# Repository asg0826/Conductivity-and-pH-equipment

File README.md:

# Conductivity-and-pH-equipment

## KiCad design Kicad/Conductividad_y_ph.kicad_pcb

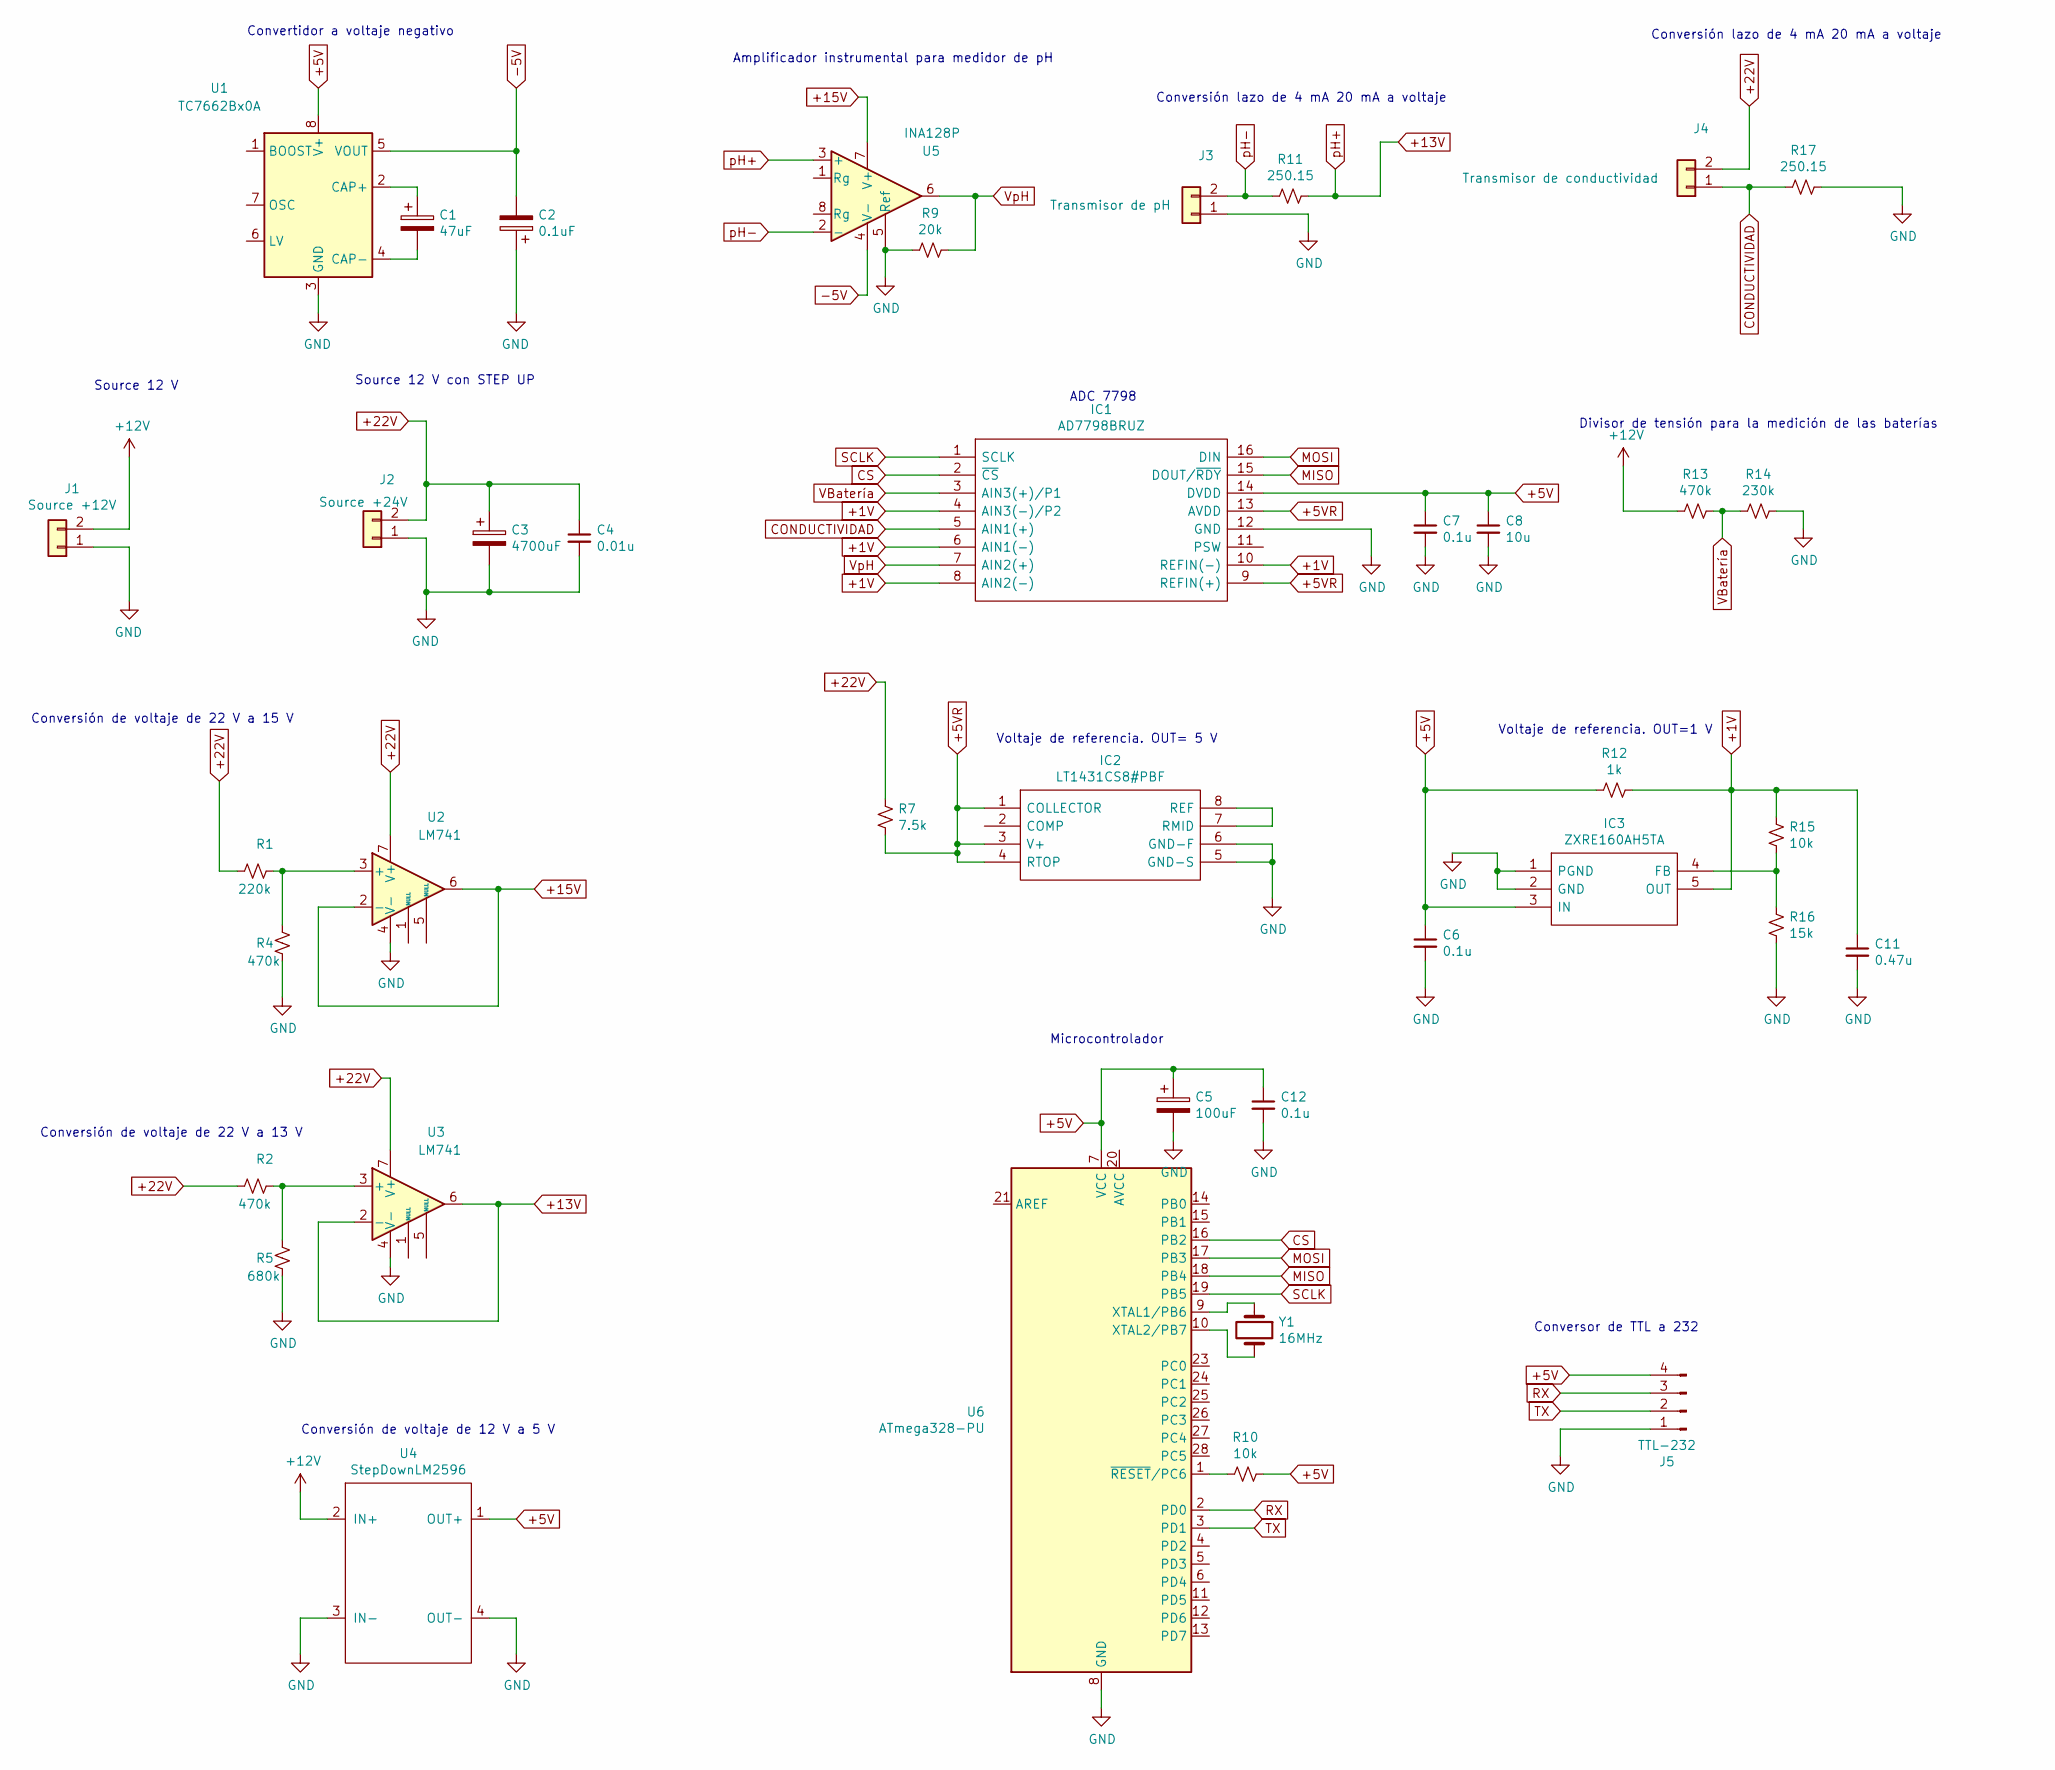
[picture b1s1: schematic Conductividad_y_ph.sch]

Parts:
C1: 47uF; CP_Radial_D5.0mm_P2.50mm
C2: 0.1uF; CP_Radial_D5.0mm_P2.50mm
C3: 4700uF; 4700uF_footPrint
C4: 0.01u; Tantalum_5.08mm
C5: 100uF; CP_Radial_D5.0mm_P2.50mm
C6, C7, C12: 0.1u; Tantalum_5.08mm
C8: 10u; Tantalum_5.08mm
C11: 0.47u; Tantalum_5.08mm
IC1: AD7798BRUZ; AD7798; Manufacturer_Part_Number AD7798BRUZ; Mouser Part Number 584-AD7798BRUZ
IC2: LT1431CS8#PBF; DIP-8_W7.62mm_Socket; Manufacturer_Part_Number LT1431CS8#PBF; Mouser Part Number 584-LT1431CS8#PBF
IC3: ZXRE160AH5TA; Regulator1V3; Manufacturer_Part_Number ZXRE160AH5TA; Mouser Part Number 522-ZXRE160AH5TA
J1: Source +12V; Conector2
J2: Source +24V; Conector2
J3: Transmisor de pH; Conector2
J4: Transmisor de conductividad; Conector2
J5: TTL-232; FanPinHeader_1x04_P2.54mm_Vertical
R1: 220k; R_Axial_DIN0207_L6.3mm_D2.5mm_P7.62mm_Horizontal
R2, R4, R13: 470k; R_Axial_DIN0207_L6.3mm_D2.5mm_P7.62mm_Horizontal
R5: 680k; R_Axial_DIN0207_L6.3mm_D2.5mm_P7.62mm_Horizontal
R7: 7.5k; R_Axial_DIN0207_L6.3mm_D2.5mm_P7.62mm_Horizontal
R9: 20k; R_Axial_DIN0207_L6.3mm_D2.5mm_P7.62mm_Horizontal
R10, R15: 10k; R_Axial_DIN0207_L6.3mm_D2.5mm_P7.62mm_Horizontal
R11, R17: 250.15; R_Axial_DIN0207_L6.3mm_D2.5mm_P15.24mm_Horizontal
R12: 1k; R_Axial_DIN0207_L6.3mm_D2.5mm_P7.62mm_Horizontal
R14: 230k; R_Axial_DIN0207_L6.3mm_D2.5mm_P7.62mm_Horizontal
R16: 15k; R_Axial_DIN0207_L6.3mm_D2.5mm_P7.62mm_Horizontal
U1: TC7662Bx0A; DIP-8_W7.62mm_Socket
U2, U3: LM741; DIP-8_W7.62mm_Socket
U4: StepDownLM2596; StepDownLm2596
U5: INA128P; DIP-8_W7.62mm_Socket
U6: ATmega328-PU; DIP-28_W7.62mm
Y1: 16MHz; Oscillator_16Mhz

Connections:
+1V: C11.1, IC1.4 (AIN3(-)/P2), IC1.6 (AIN1(-)), IC1.8 (AIN2(-)), IC1.10 (REFIN(-)), IC3.5 (OUT), R12.1, R15.1
+5V: C5.1, C6.1, C7.1, C8.1, C12.1, IC1.14 (DVDD), IC3.3 (IN), J5.4, R10.1, R12.2, U1.8 (V+), U4.1 (OUT+), U6.7 (VCC)
+5VR: IC1.9 (REFIN(+)), IC1.13 (AVDD), IC2.1 (COLLECTOR), IC2.3 (V+), IC2.4 (RTOP), R7.2
+12V: J1.2, R13.2, U4.2 (IN+); also elsewhere on the board
+13V: R11.1, U3.2 (-), U3.6, U5.3 (+)
+15V: U2.2 (-), U2.6, U5.7 (V+)
+22V: C3.1, C4.1, J2.2, J4.2, R1.2, R2.2, R7.1, U2.7 (V+), U3.7 (V+)
-5V: C2.2, U1.5 (VOUT), U5.4 (V-)
CONDUCTIVIDAD: IC1.5 (AIN1(+)), J4.1, R17.2
CS: IC1.2 (~CS), U6.16 (PB2)
GND: C2.1, C3.2, C4.2, C5.2, C6.2, C7.2, C8.2, C11.2, C12.2, IC1.12 (GND), IC2.5 (GND-S), IC2.6 (GND-F), IC3.1 (PGND), IC3.2 (GND), J1.1, J2.1, J3.1, J5.1, R4.2, R5.2, R9.2, R14.1, R16.2, R17.1, U1.3 (GND), U2.4 (V-), U3.4 (V-), U4.3 (IN-), U4.4 (OUT-), U5.5 (Ref), U6.8 (GND), U6.22 (GND); also elsewhere on the board
MISO: IC1.15 (DOUT/~RDY), U6.18 (PB4)
MOSI: IC1.16 (DIN), U6.17 (PB3)
unnamed: C1.1, U1.2 (CAP+)
unnamed: C1.2, U1.4 (CAP-)
unnamed: IC2.7 (RMID), IC2.8 (REF)
unnamed: IC3.4 (FB), R15.2, R16.1
unnamed: R1.1, R4.1, U2.3 (+)
unnamed: R2.1, R5.1, U3.3 (+)
unnamed: R10.2, U6.1 (~RESET~/PC6)
unnamed: U6.9 (XTAL1/PB6), Y1.1
unnamed: U6.10 (XTAL2/PB7), Y1.2
RX: J5.3, U6.2 (PD0)
SCLK: IC1.1 (SCLK), U6.19 (PB5)
TX: J5.2, U6.3 (PD1)
VBatería: IC1.3 (AIN3(+)/P1), R13.1, R14.2
VpH: IC1.7 (AIN2(+)), R9.1, U5.6
pH-: J3.2, R11.2, U5.2 (-)

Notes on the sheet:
Divisor de tensión para la medición de las baterías
Voltaje de referencia. OUT= 5 V
Voltaje de referencia. OUT=1 V
ADC 7798
Source 12 V
Amplificador instrumental para medidor de pH
Conversión lazo de 4 mA 20 mA a voltaje
Conversor de TTL a 232
Conversión de voltaje de 12 V a 5 V
Conversión de voltaje de 22 V a 13 V
Conversión de voltaje de 22 V a 15 V
Source 12 V con STEP UP
Microcontrolador
Convertidor a voltaje negativo

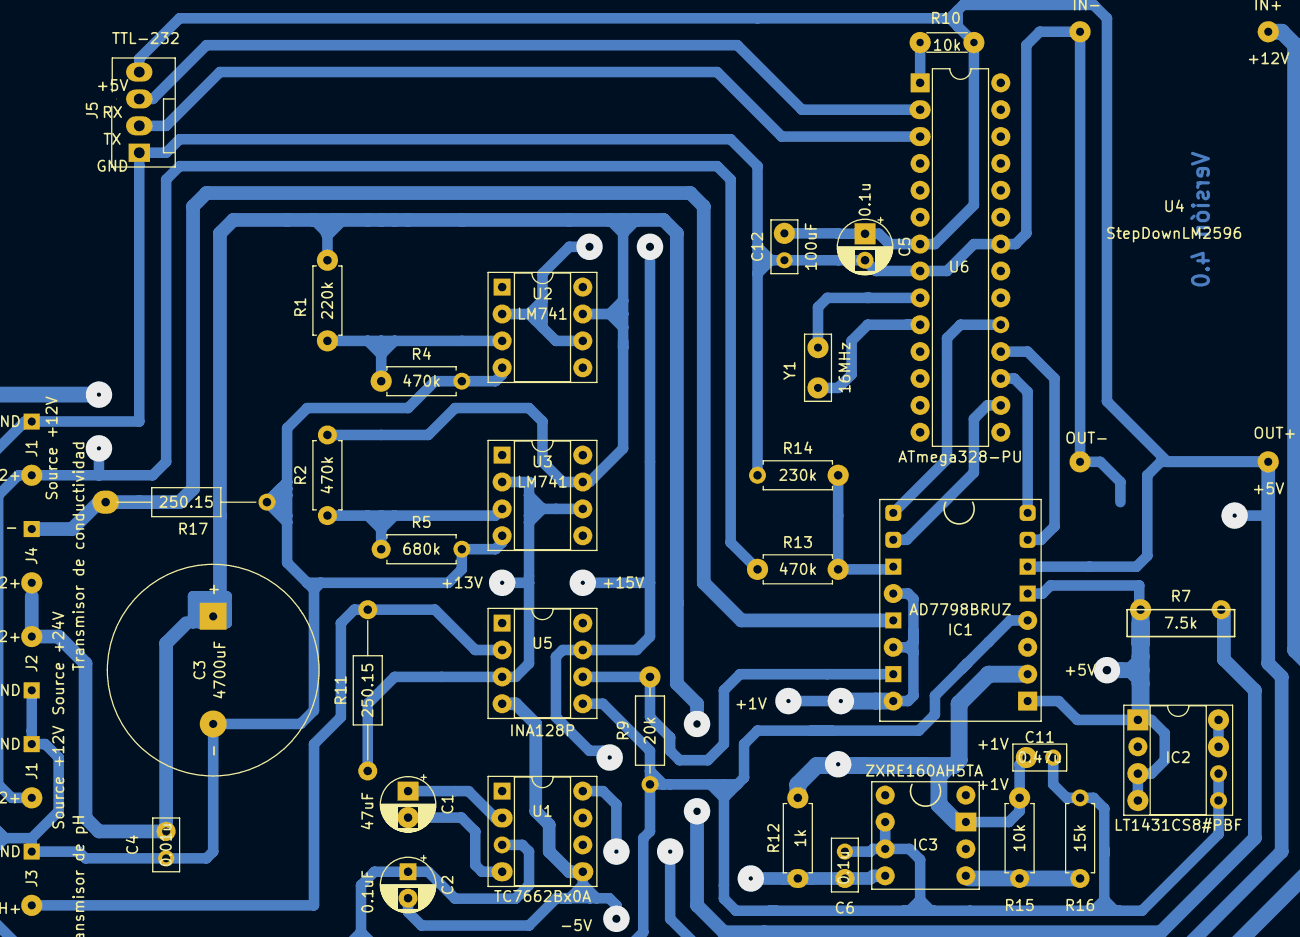
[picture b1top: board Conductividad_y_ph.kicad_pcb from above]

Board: 2 copper layers, 38 parts (1 on the bottom side), 28 nets.

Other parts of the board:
J1#2: Source +12V; Conector2

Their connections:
+12V: J1#2.2; also elsewhere on the board
GND: J1#2.1; also elsewhere on the board
